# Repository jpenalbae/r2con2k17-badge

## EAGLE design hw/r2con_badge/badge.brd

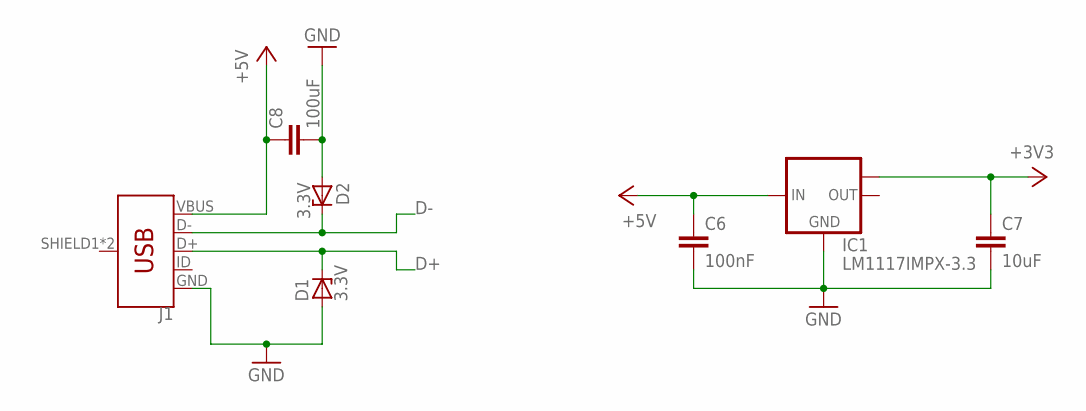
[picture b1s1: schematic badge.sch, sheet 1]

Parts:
C6: 100nF; C0805
C7: 10uF; C0805
C8: 100uF; C1206
D1, D2: 3.3V; SOD80C
IC1: LM1117IMPX-3.3; SOT223
J1: USB_MICRO-B_FEMALE-SMT; USB-B-MICRO-SMD

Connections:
+3V3: C7.1, IC1.TAB (OUT1); also elsewhere on the board
+5V: C6.1, C8.1, IC1.3 (IN), J1.VBUS; also elsewhere on the board
D+: D1.C, J1.D+; also elsewhere on the board
D-: D2.C, J1.D-; also elsewhere on the board
GND: C6.2, C7.2, C8.2, D1.A, D2.A, IC1.1 (GND), J1.GND; also elsewhere on the board

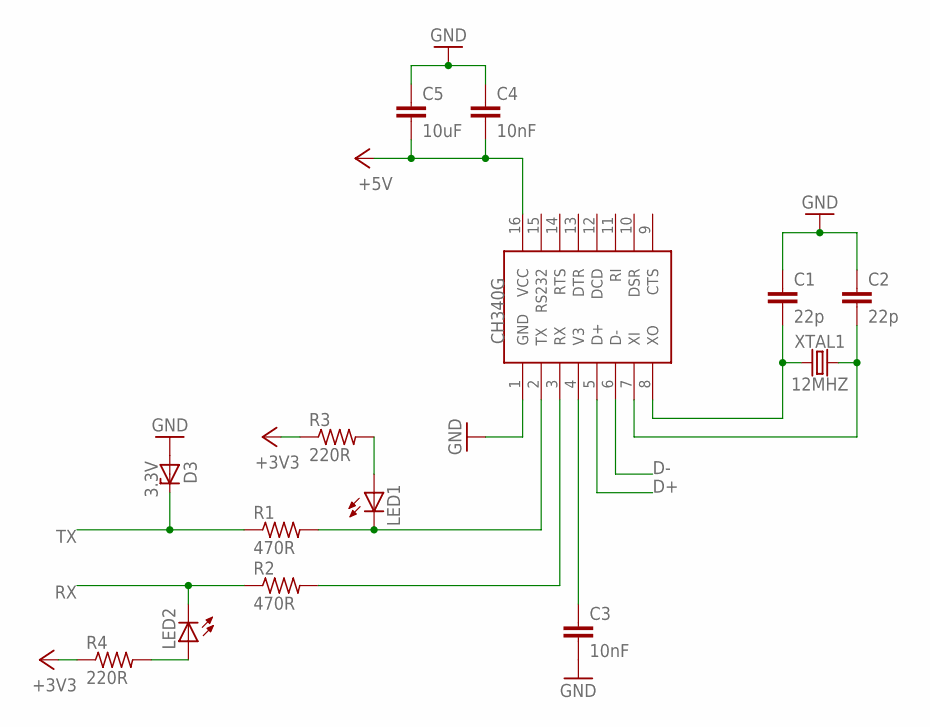
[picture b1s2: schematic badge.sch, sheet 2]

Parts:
C1, C2: 22p; C0805
C3, C4: 10nF; C0805
C5: 10uF; C0805
D3: 3.3V; SOD80C
LED1, LED2: LEDSML0805; SML0805
R1, R2: 470R; R0805
R3, R4: 220R; M0805
U$2: CH340G; SOIC16
XTAL1: 12MHZ; HC49UP

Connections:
+3V3: R3.1, R4.1; also elsewhere on the board
+5V: C4.2, C5.2, U$2.16 (VCC); also elsewhere on the board
CH_RX: R2.2, U$2.3 (RX)
CH_TX: LED1.C, R1.2, U$2.2 (TX)
D+: U$2.5 (D+); also elsewhere on the board
D-: U$2.6 (D-); also elsewhere on the board
GND: C1.1, C2.1, C3.2, C4.1, C5.1, D3.A, U$2.1 (GND); also elsewhere on the board
unnamed: LED1.A, R3.2
unnamed: LED2.A, R4.2
RX: LED2.C, R2.1; also elsewhere on the board
TX: D3.C, R1.1; also elsewhere on the board
V3: C3.1, U$2.4 (V3)
XI: C2.2, U$2.7 (XI), XTAL1.2
XO: C1.2, U$2.8 (XO), XTAL1.1

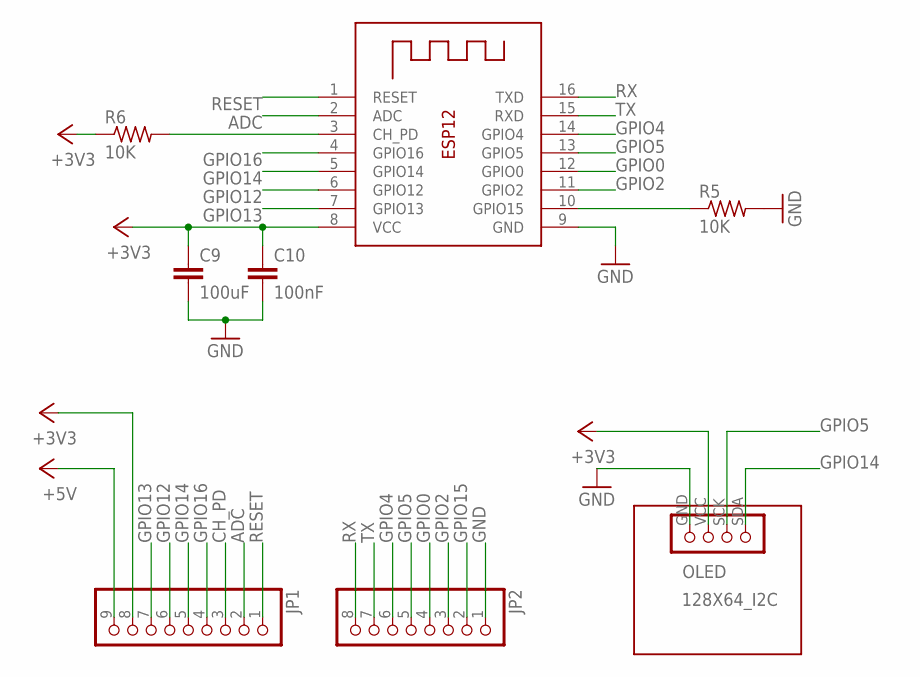
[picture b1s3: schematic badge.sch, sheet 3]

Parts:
C9: 100uF; C1206
C10: 100nF; C0805
JP1: PINHD-1X9; 1X09
JP2: PINHD-1X8; 1X08
OLED: 128X64_I2C
R5, R6: 10K; R0805
X2: ESP-12F; ESP-12

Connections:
+3V3: C9.1, C10.1, JP1.8, OLED.VCC, R6.1, X2.8 (VCC); also elsewhere on the board
+5V: JP1.9; also elsewhere on the board
ADC: JP1.2, X2.2 (ADC)
CH_PD: JP1.3, R6.2, X2.3 (CH_PD)
GND: C9.2, C10.2, JP2.1, OLED.GND, R5.2, X2.9 (GND); also elsewhere on the board
GPIO0: JP2.4, X2.12 (GPIO0); also elsewhere on the board
GPIO2: JP2.3, X2.11 (GPIO2)
GPIO4: JP2.6, X2.14 (GPIO4); also elsewhere on the board
GPIO5: JP2.5, OLED.SCK, X2.13 (GPIO5)
GPIO12: JP1.6, X2.6 (GPIO12); also elsewhere on the board
GPIO13: JP1.7, X2.7 (GPIO13)
GPIO14: JP1.5, OLED.SDA, X2.5 (GPIO14)
GPIO15: JP2.2, R5.1, X2.10 (GPIO15)
GPIO16: JP1.4, X2.4 (GPIO16)
RESET: JP1.1, X2.1 (RESET); also elsewhere on the board
RX: JP2.8, X2.16 (TXD); also elsewhere on the board
TX: JP2.7, X2.15 (RXD); also elsewhere on the board

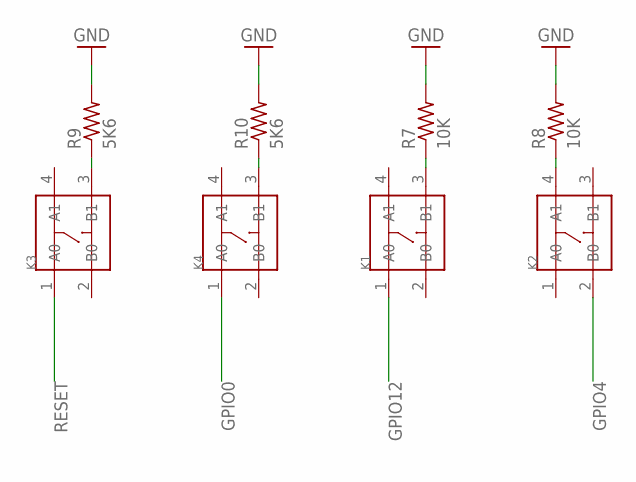
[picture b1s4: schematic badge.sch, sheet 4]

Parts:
K1, K2, K3, K4: SMD-SWITCH-TACTILE-SPST-NO(4P-D6.0MM); SW4-SMD-6.0X6.0X5.0MM
R7, R8: 10K; R0805
R9, R10: 5K6; R0805

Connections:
GND: R7.2, R8.2, R9.2, R10.2; also elsewhere on the board
GPIO0: K4.1 (A0); also elsewhere on the board
GPIO4: K2.2 (B0); also elsewhere on the board
GPIO12: K1.1 (A0); also elsewhere on the board
unnamed: K3.3 (B1), R9.1
unnamed: K4.3 (B1), R10.1
unnamed: K2.4 (A1), R8.1
unnamed: K1.3 (B1), R7.1
RESET: K3.1 (A0); also elsewhere on the board

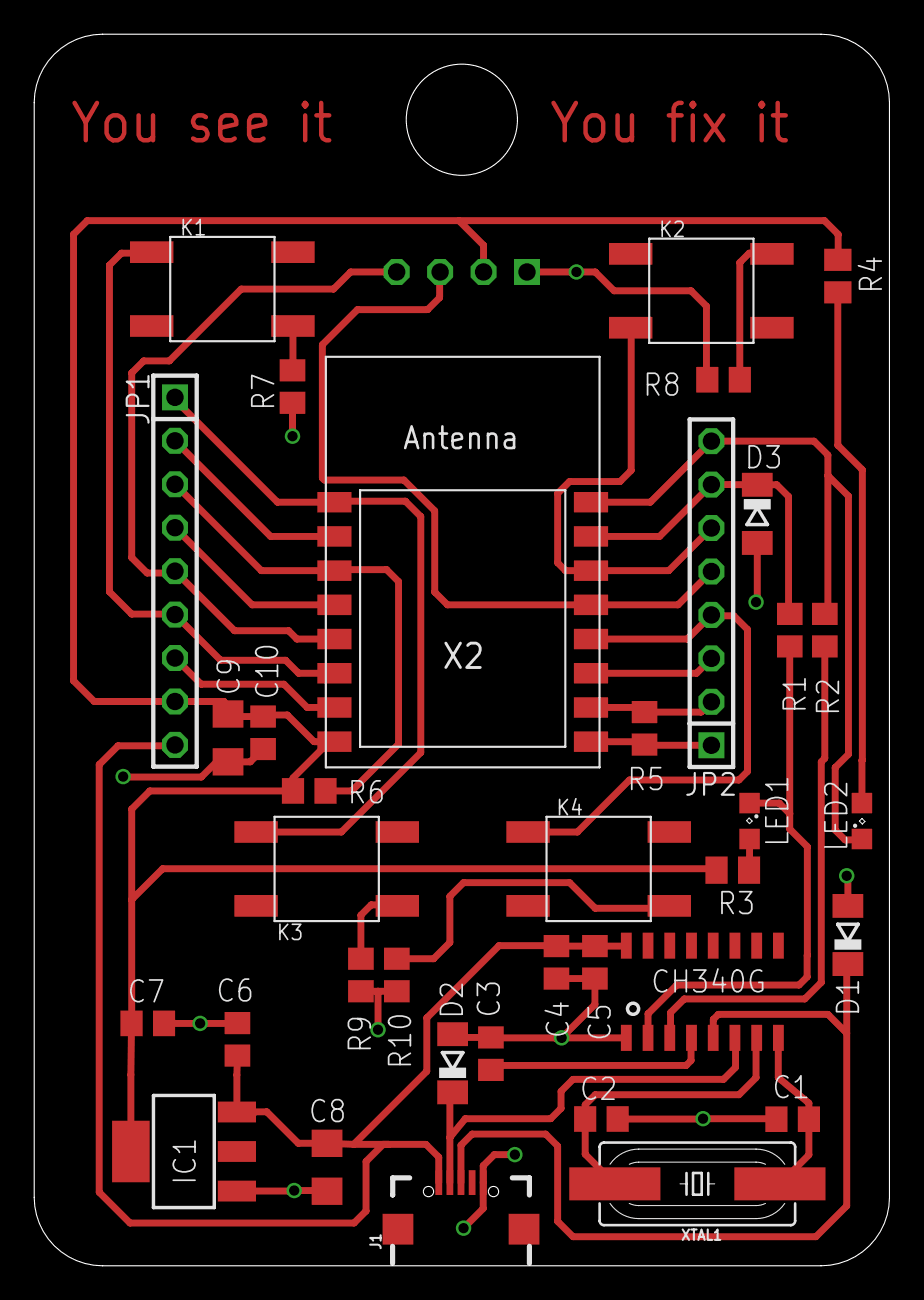
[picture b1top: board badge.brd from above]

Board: 2 copper layers, 50.0 x 72.0 mm, 37 parts (1 on the bottom side), 30 nets.

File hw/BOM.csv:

Qty,Value,Device,Package,Parts,Description,MPN,PROD_ID
2,,LEDSML0805,SML0805,"LED1, LED2",LED,,
1,,PINHD-1X8,1X08,JP2,PIN HEADER,,
1,,PINHD-1X9,1X09,JP1,PIN HEADER,,
4,,SMD-SWITCH-TACTILE-SPST-NO(4P-D6.0MM),SW4-SMD-6.0X6.0X5.0MM,"K1, K2, K3, K4",6x6 MM Tactile switch,DTSM-62K-S-V-T/R(SN431),
1,,USB_MICRO-B_FEMALE-SMT,USB-B-MICRO-SMD,J1,USB Type Micro-B Connector,,CONN-11752
2,100nF,C-EUC0805,C0805,"C6, C10","CAPACITOR, European symbol",,
2,100uF,C-EUC1206,C1206,"C8, C9","CAPACITOR, European symbol",,
4,10K,R-US_R0805,R0805,"R5, R6, R7, R8","RESISTOR, American symbol",,
2,10nF,C-EUC0805,C0805,"C3, C4","CAPACITOR, European symbol",,
2,10uF,C-EUC0805,C0805,"C5, C7","CAPACITOR, European symbol",,
1,128X64_I2C,OLED_128X64_I2C 0.96”,128X64_I2C,OLED,128x64 0.96” I2C OLED Screen,,
1,12MHZ,CRYSTALSMD-HC49UP,HC49UP,XTAL1,Crystals (Generic),,
2,220R,R-US_M0805,M0805,"R3, R4","RESISTOR, American symbol",,
2,22p,C-EUC0805,C0805,"C1, C2","CAPACITOR, European symbol",,
3,3.3V,ZENER-DIODESOD80C,SOD80C,"D1, D2, D3",Z-Diode,,
2,470R,R-US_R0805,R0805,"R1, R2","RESISTOR, American symbol",,
2,5K6,R-US_R0805,R0805,"R9, R10","RESISTOR, American symbol",,
1,CH340G,CH340G,SOIC16,U$2,USB to UART,,
1,ESP-12F,ESP-12,ESP-12,X2,,,
1,LM1117IMPX-3.3,AMS1117-3.3V,SOT223,IC1,Linear voltage regulator,,

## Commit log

2017-08-31 Upload badge software
2017-08-31 Add hardware design files
2018-01-05 Update schematics, and add BOM

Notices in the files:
parts and their libraries:
SparkFun-Clocks: Licensing: Creative Commons ShareAlike 4.0 International - https://creativecommons.org/licenses/by-sa/4.0
